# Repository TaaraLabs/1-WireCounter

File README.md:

1-Wire Counter
====================

[WebSite](https://taaralabs.eu/oc1)

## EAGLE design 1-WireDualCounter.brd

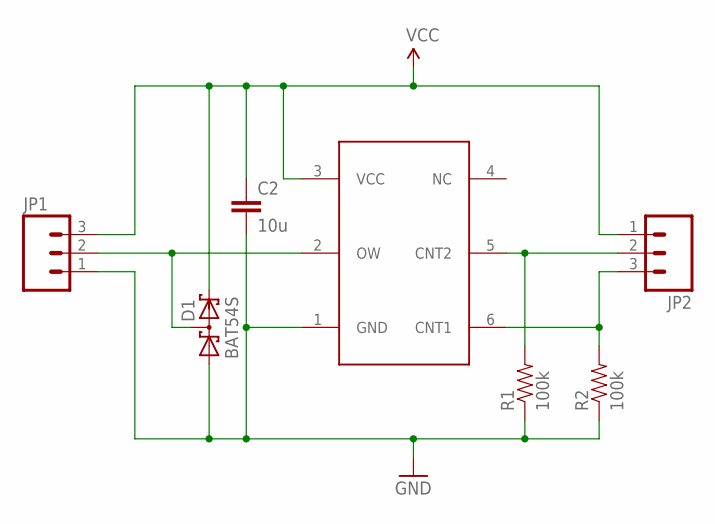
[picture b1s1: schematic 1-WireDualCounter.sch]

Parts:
C2: 10u; 0603-CAP
D1: BAT54S; SOT23
JP1, JP2: M03LOCK; 1X03_LOCK
R1, R2: 100k; 0603-RES
U$2: DS2423P; TSOC6

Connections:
GND: C2.2, D1.1 (A1), JP1.1, R1.1, R2.1, U$2.1 (GND)
unnamed: D1.3 (C1A2), JP1.2, U$2.2 (OW)
unnamed: JP2.2, R1.2, U$2.5 (CNT2)
unnamed: JP2.3, R2.2, U$2.6 (CNT1)
VCC: C2.1, D1.2 (C2), JP1.3, JP2.1, U$2.3 (VCC)

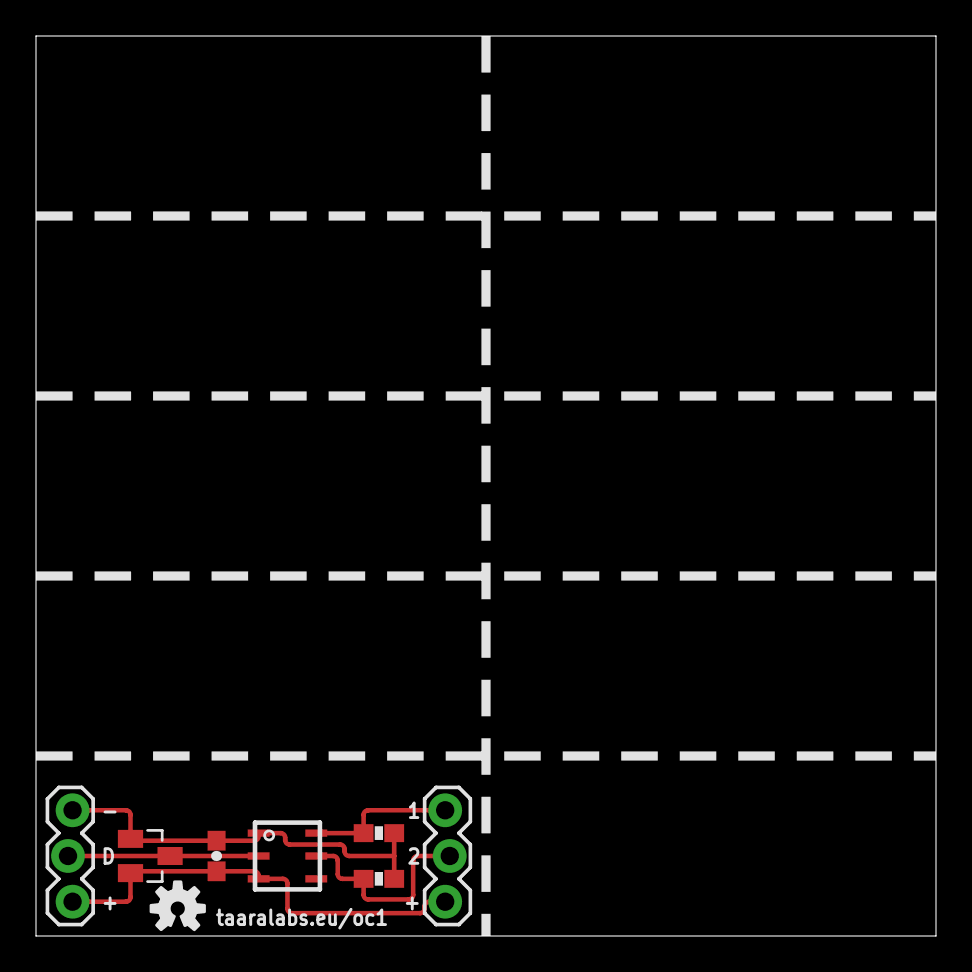
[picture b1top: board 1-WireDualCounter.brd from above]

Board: 2 copper layers, 50.0 x 50.0 mm, 8 parts (0 on the bottom side), 5 nets.

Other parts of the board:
U$1: OSHW-LOGO-S

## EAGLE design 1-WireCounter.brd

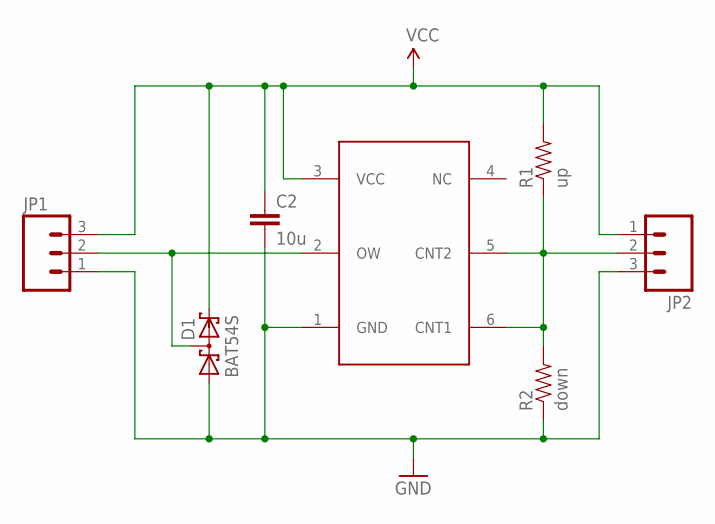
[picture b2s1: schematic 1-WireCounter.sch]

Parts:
C2: 10u; 0603-CAP
D1: BAT54S; SOT23
JP1, JP2: M03LOCK; 1X03_LOCK
R1: up; 0603-RES
R2: down; 0603-RES
U$2: DS2423P; TSOC6

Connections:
GND: C2.2, D1.1 (A1), JP1.1, JP2.3, R2.1, U$2.1 (GND)
unnamed: D1.3 (C1A2), JP1.2, U$2.2 (OW)
unnamed: JP2.2, R1.1, R2.2, U$2.5 (CNT2), U$2.6 (CNT1)
VCC: C2.1, D1.2 (C2), JP1.3, JP2.1, R1.2, U$2.3 (VCC)

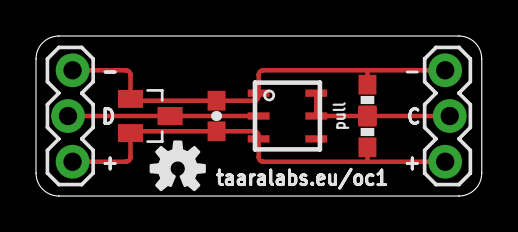
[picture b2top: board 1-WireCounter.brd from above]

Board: 2 copper layers, 24.8 x 8.9 mm, 9 parts (1 on the bottom side), 4 nets.

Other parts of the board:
U$1, U$3: OSHW-LOGO-S

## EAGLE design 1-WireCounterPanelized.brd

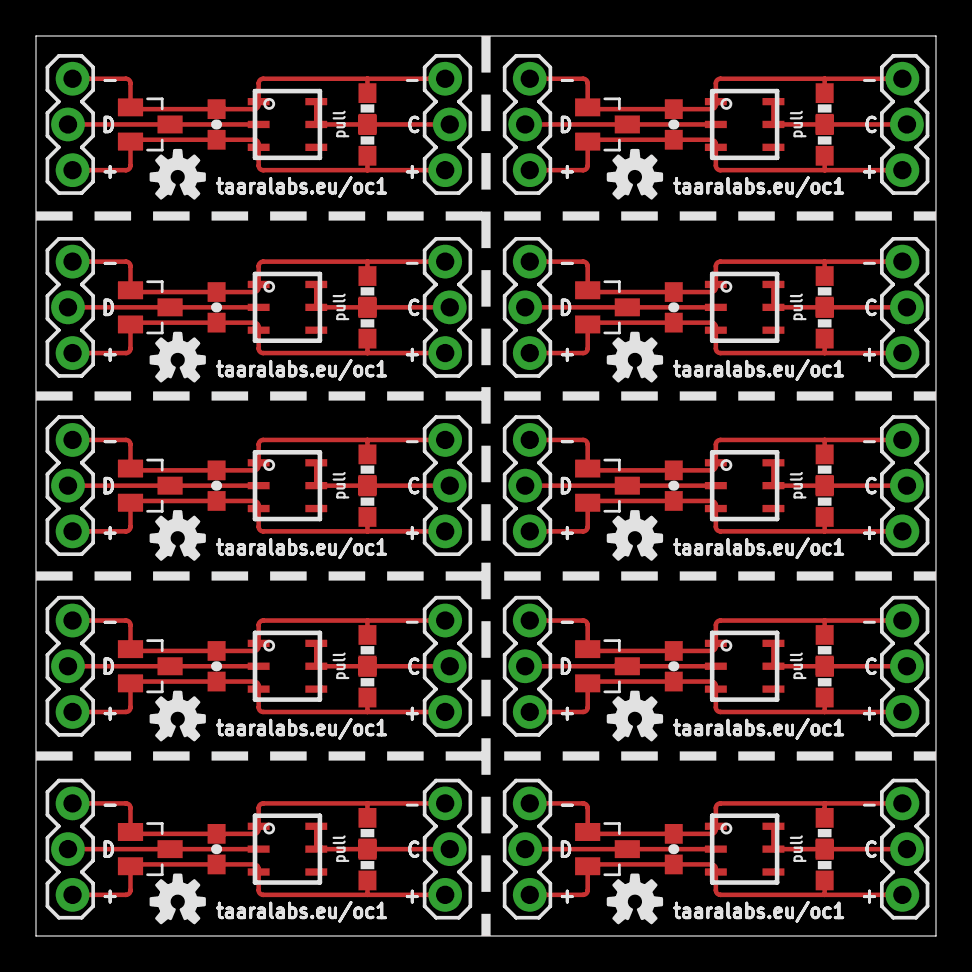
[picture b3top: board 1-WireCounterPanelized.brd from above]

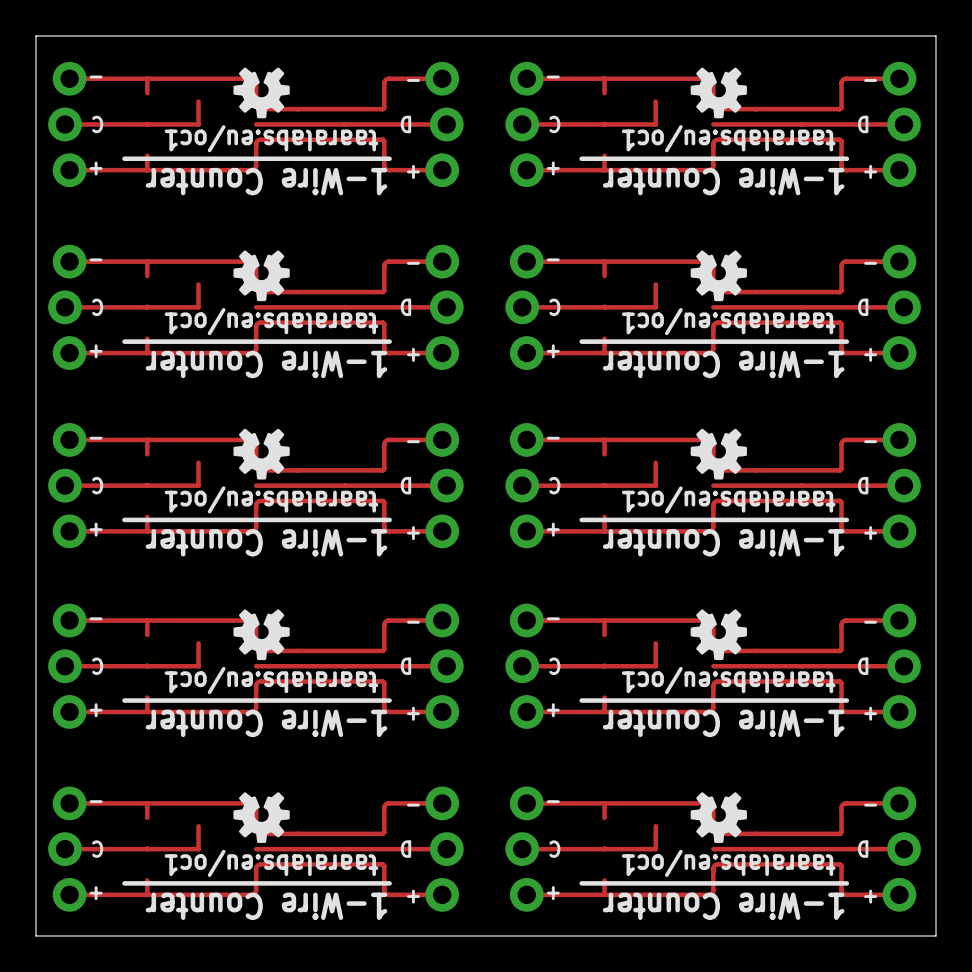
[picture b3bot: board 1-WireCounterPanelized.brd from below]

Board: 2 copper layers, 50.0 x 50.0 mm, 90 parts (10 on the bottom side), 40 nets.

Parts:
C1, C2, C3, C4, C5, C6, C7, C8, C9, C10: 10u; 0603-CAP
D1, D2, D3, D4, D5, D6, D7, D8, D9, D10: BAT54S; SOT23
JP1, JP2, JP3, JP4, JP5, JP6, JP7, JP8, JP9, JP10, JP11, JP12, JP13, JP14, JP15, JP16, JP17, JP18, JP19, JP20: 1X03_LOCK
R1, R4, R6, R8, R10, R12, R14, R16, R18, R20: up; 0603-RES
R2, R3, R5, R7, R9, R11, R13, R15, R17, R19: down; 0603-RES
U$1, U$3, U$5, U$6, U$8, U$9, U$11, U$12, U$14, U$15, U$17, U$18, U$20, U$21, U$23, U$24, U$26, U$27, U$29, U$30: OSHW-LOGO-S
U$2, U$4, U$7, U$10, U$13, U$16, U$19, U$22, U$25, U$28: DS2423P; TSOC6

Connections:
GND: C2.2, D1.1, JP1.1, JP2.3, R2.1, U$2.1
GND1: C1.2, D2.1, JP3.1, JP4.3, R3.1, U$4.1
GND2: C3.2, D3.1, JP5.1, JP6.3, R5.1, U$7.1
GND3: C4.2, D4.1, JP7.1, JP8.3, R7.1, U$10.1
GND4: C5.2, D5.1, JP9.1, JP10.3, R9.1, U$13.1
GND5: C6.2, D6.1, JP11.1, JP12.3, R11.1, U$16.1
GND6: C7.2, D7.1, JP13.1, JP14.3, R13.1, U$19.1
GND7: C8.2, D8.1, JP15.1, JP16.3, R15.1, U$22.1
GND8: C9.2, D9.1, JP17.1, JP18.3, R17.1, U$25.1
GND9: C10.2, D10.1, JP19.1, JP20.3, R19.1, U$28.1
unnamed: D1.3, JP1.2, U$2.2
unnamed: D2.3, JP3.2, U$4.2
unnamed: JP4.2, R3.2, R4.1, U$4.5, U$4.6
unnamed: D3.3, JP5.2, U$7.2
unnamed: JP2.2, R1.1, R2.2, U$2.5, U$2.6
unnamed: JP6.2, R5.2, R6.1, U$7.5, U$7.6
unnamed: D4.3, JP7.2, U$10.2
unnamed: JP8.2, R7.2, R8.1, U$10.5, U$10.6
unnamed: D5.3, JP9.2, U$13.2
unnamed: JP10.2, R9.2, R10.1, U$13.5, U$13.6
unnamed: D6.3, JP11.2, U$16.2
unnamed: JP12.2, R11.2, R12.1, U$16.5, U$16.6
unnamed: D7.3, JP13.2, U$19.2
unnamed: JP14.2, R13.2, R14.1, U$19.5, U$19.6
unnamed: D8.3, JP15.2, U$22.2
unnamed: JP16.2, R15.2, R16.1, U$22.5, U$22.6
unnamed: D9.3, JP17.2, U$25.2
unnamed: JP18.2, R17.2, R18.1, U$25.5, U$25.6
unnamed: D10.3, JP19.2, U$28.2
unnamed: JP20.2, R19.2, R20.1, U$28.5, U$28.6
VCC: C2.1, D1.2, JP1.3, JP2.1, R1.2, U$2.3
VCC1: C1.1, D2.2, JP3.3, JP4.1, R4.2, U$4.3
VCC2: C3.1, D3.2, JP5.3, JP6.1, R6.2, U$7.3
VCC3: C4.1, D4.2, JP7.3, JP8.1, R8.2, U$10.3
VCC4: C5.1, D5.2, JP9.3, JP10.1, R10.2, U$13.3
VCC5: C6.1, D6.2, JP11.3, JP12.1, R12.2, U$16.3
VCC6: C7.1, D7.2, JP13.3, JP14.1, R14.2, U$19.3
VCC7: C8.1, D8.2, JP15.3, JP16.1, R16.2, U$22.3
VCC8: C9.1, D9.2, JP17.3, JP18.1, R18.2, U$25.3
VCC9: C10.1, D10.2, JP19.3, JP20.1, R20.2, U$28.3

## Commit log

2015-01-22 :lollipop: Added .gitattributes & .gitignore files
2015-01-22 1-Wire Counter
2015-01-24 README.md created

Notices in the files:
parts and their libraries:
SparkFun: Licensing: CC v3.0 Share-Alike You are welcome to use this library for commercial purposes.
